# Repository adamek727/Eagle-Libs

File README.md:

# Eagle-Libs
My set of eagle libraries

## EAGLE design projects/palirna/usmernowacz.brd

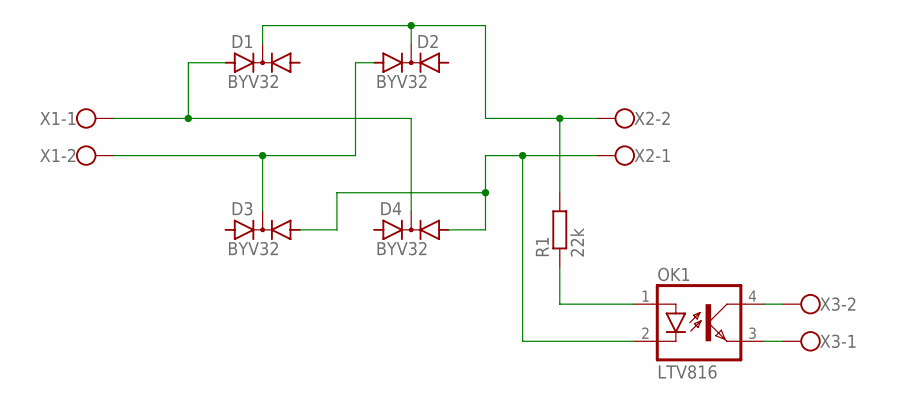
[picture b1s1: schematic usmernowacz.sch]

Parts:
D1, D2, D3, D4: BYV32; TO220ABS
OK1: LTV816; DIL04
R1: 22k; R1206
X1, X2, X3: W237-102

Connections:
unnamed: D1.A1, D4.C, X1.1
unnamed: D1.C, D2.C, R1.2, X2.2
unnamed: D2.A1, D3.C, X1.2
unnamed: D3.A2, D4.A2, OK1.2 (C), X2.1
unnamed: OK1.1 (A), R1.1
unnamed: OK1.3 (EMIT), X3.1
unnamed: OK1.4 (COL), X3.2

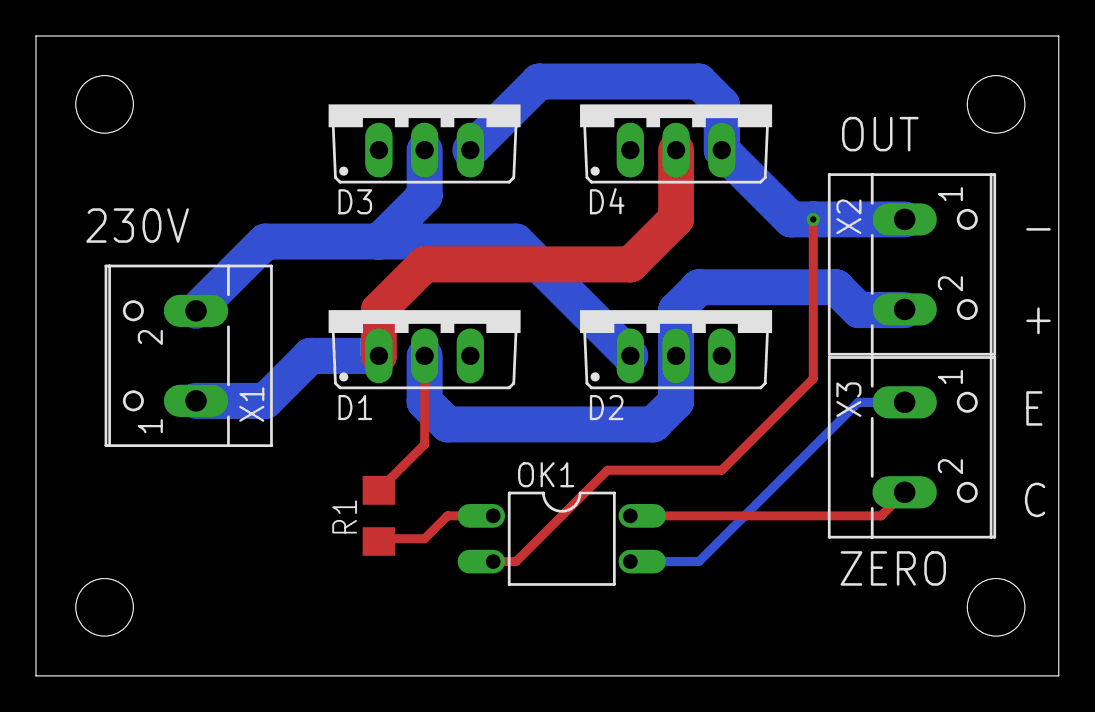
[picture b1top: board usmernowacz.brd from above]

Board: 2 copper layers, 56.8 x 35.5 mm, 9 parts (0 on the bottom side), 7 nets.

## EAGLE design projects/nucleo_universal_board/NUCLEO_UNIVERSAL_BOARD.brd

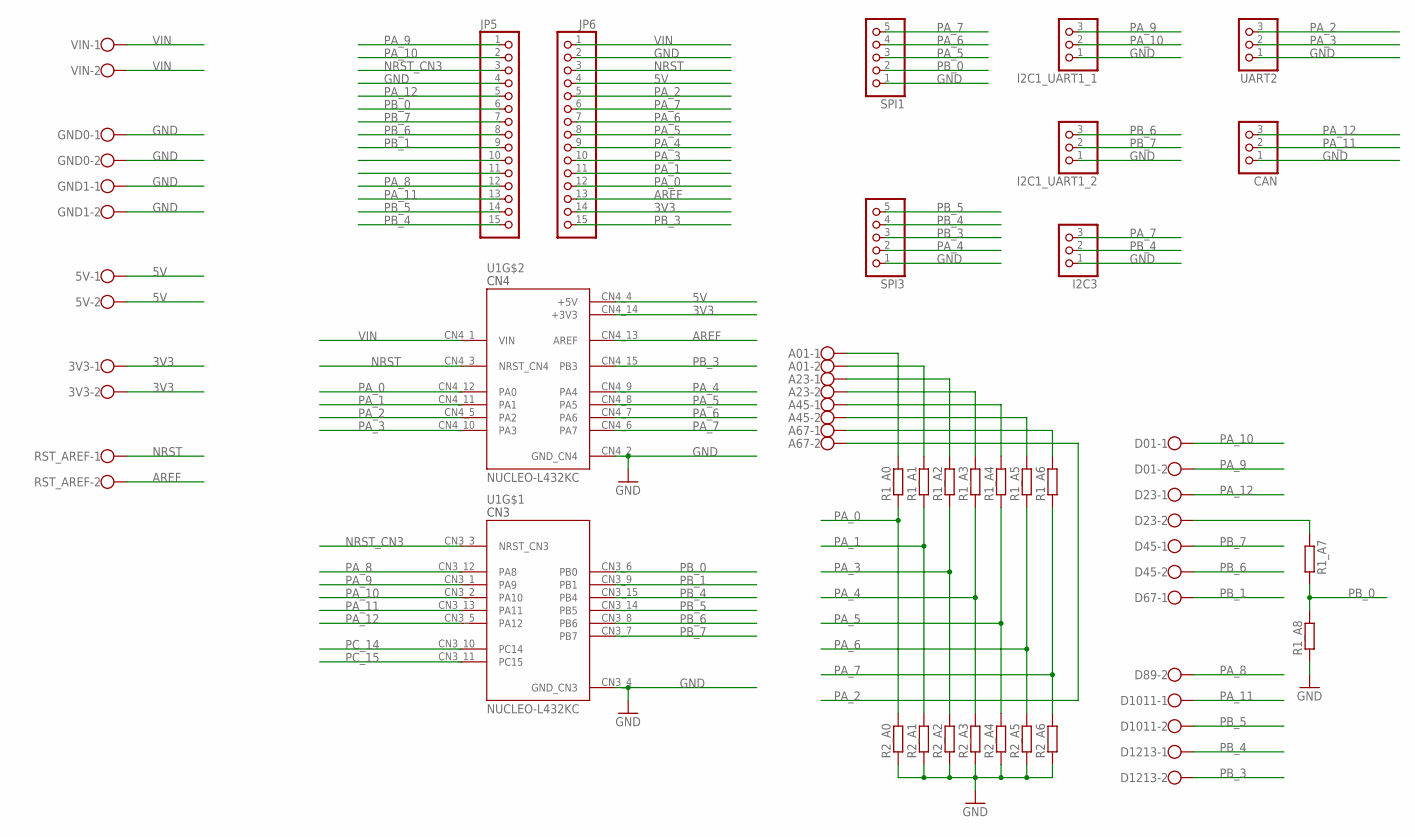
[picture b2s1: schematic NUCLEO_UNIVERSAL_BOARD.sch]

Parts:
3V3, 5V: W237-102
A01, A23, A45, A67: W237-102
CAN: PINHD-1X3; 1X03
D01, D23, D45, D67, D89, D1011, D1213: W237-102
GND0, GND1: W237-102
I2C1_UART1_1, I2C1_UART1_2, I2C3: PINHD-1X3; 1X03
JP5, JP6: PINHD-1X15; 1X15
R1_A0, R1_A1, R1_A2, R1_A3, R1_A4, R1_A5, R1_A6, R1_A7, R1_A8, R2_A0, R2_A1, R2_A2, R2_A3, R2_A4, R2_A5, R2_A6: R-EU_M1206; M1206
RST_AREF: W237-102
SPI1, SPI3: PINHD-1X5; 1X05
U1: NUCLEO-L432KC; MODULE_NUCLEO-L432KC
UART2: PINHD-1X3; 1X03
VIN: W237-102

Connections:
3V3: 3V3.1, 3V3.2, JP6.14, U1.CN4_14 (+3V3)
5V: 5V.1, 5V.2, JP6.4, U1.CN4_4 (+5V)
AREF: JP6.13, RST_AREF.2, U1.CN4_13 (AREF)
GND: CAN.1, GND0.1, GND0.2, GND1.1, GND1.2, I2C1_UART1_1.1, I2C1_UART1_2.1, I2C3.1, JP5.4, JP6.2, R1_A8.1, R2_A0.1, R2_A1.1, R2_A2.1, R2_A3.1, R2_A4.1, R2_A5.1, R2_A6.1, SPI1.1, SPI3.1, U1.CN3_4 (GND_CN3), U1.CN4_2 (GND_CN4), UART2.1
unnamed: D23.2, R1_A7.1
unnamed: A67.1, R1_A6.2
unnamed: A45.2, R1_A5.2
unnamed: A45.1, R1_A4.2
unnamed: A23.2, R1_A3.2
unnamed: A23.1, R1_A2.2
unnamed: A01.2, R1_A1.2
unnamed: A01.1, R1_A0.2
NRST: JP6.3, RST_AREF.1, U1.CN4_3 (NRST_CN4)
NRST_CN3: JP5.3, U1.CN3_3 (NRST_CN3)
PA_0: JP6.12, R1_A0.1, R2_A0.2, U1.CN4_12 (PA0)
PA_1: JP6.11, R1_A1.1, R2_A1.2, U1.CN4_11 (PA1)
PA_2: A67.2, JP6.5, U1.CN4_5 (PA2), UART2.3
PA_3: JP6.10, R1_A2.1, R2_A2.2, U1.CN4_10 (PA3), UART2.2
PA_4: JP6.9, R1_A3.1, R2_A3.2, SPI3.2, U1.CN4_9 (PA4)
PA_5: JP6.8, R1_A4.1, R2_A4.2, SPI1.3, U1.CN4_8 (PA5)
PA_6: JP6.7, R1_A5.1, R2_A5.2, SPI1.4, U1.CN4_7 (PA6)
PA_7: I2C3.3, JP6.6, R1_A6.1, R2_A6.2, SPI1.5, U1.CN4_6 (PA7)
PA_8: D89.2, JP5.12, U1.CN3_12 (PA8)
PA_9: D01.2, I2C1_UART1_1.3, JP5.1, U1.CN3_1 (PA9)
PA_10: D01.1, I2C1_UART1_1.2, JP5.2, U1.CN3_2 (PA10)
PA_11: CAN.2, D1011.1, JP5.13, U1.CN3_13 (PA11)
PA_12: CAN.3, D23.1, JP5.5, U1.CN3_5 (PA12)
PB_0: JP5.6, R1_A7.2, R1_A8.2, SPI1.2, U1.CN3_6 (PB0)
PB_1: D67.1, JP5.9, U1.CN3_9 (PB1)
PB_3: D1213.2, JP6.15, SPI3.3, U1.CN4_15 (PB3)
PB_4: D1213.1, I2C3.2, JP5.15, SPI3.4, U1.CN3_15 (PB4)
PB_5: D1011.2, JP5.14, SPI3.5, U1.CN3_14 (PB5)
PB_6: D45.2, I2C1_UART1_2.3, JP5.8, U1.CN3_8 (PB6)
PB_7: D45.1, I2C1_UART1_2.2, JP5.7, U1.CN3_7 (PB7)
PC_14: U1.CN3_10 (PC14)
PC_15: U1.CN3_11 (PC15)
VIN: JP6.1, U1.CN4_1 (VIN), VIN.1, VIN.2

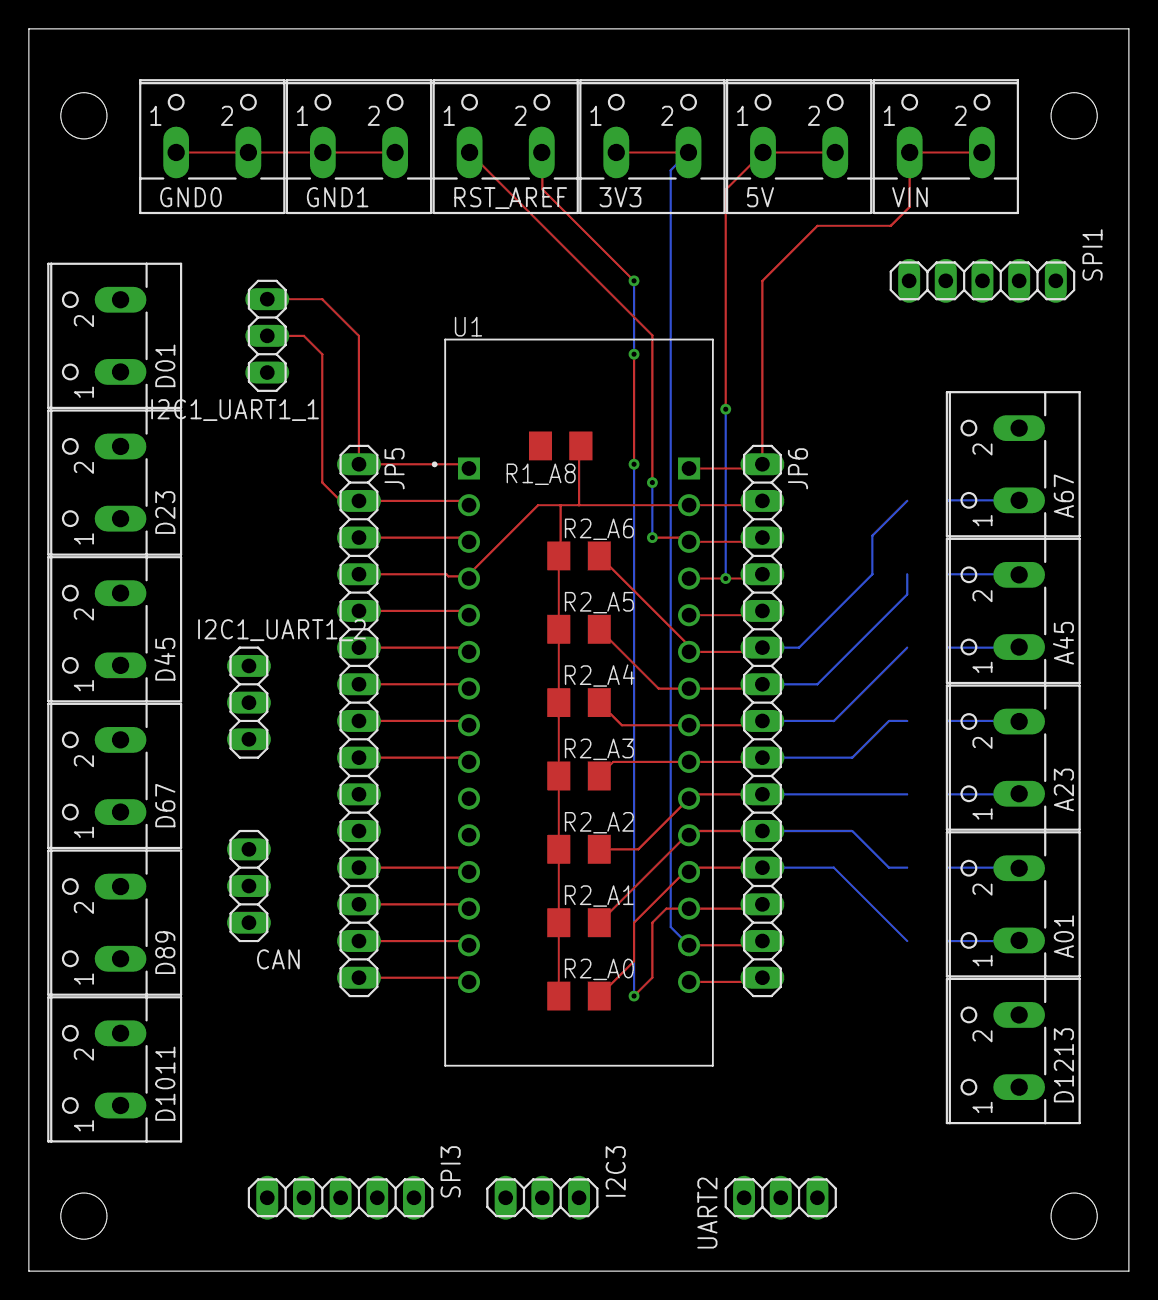
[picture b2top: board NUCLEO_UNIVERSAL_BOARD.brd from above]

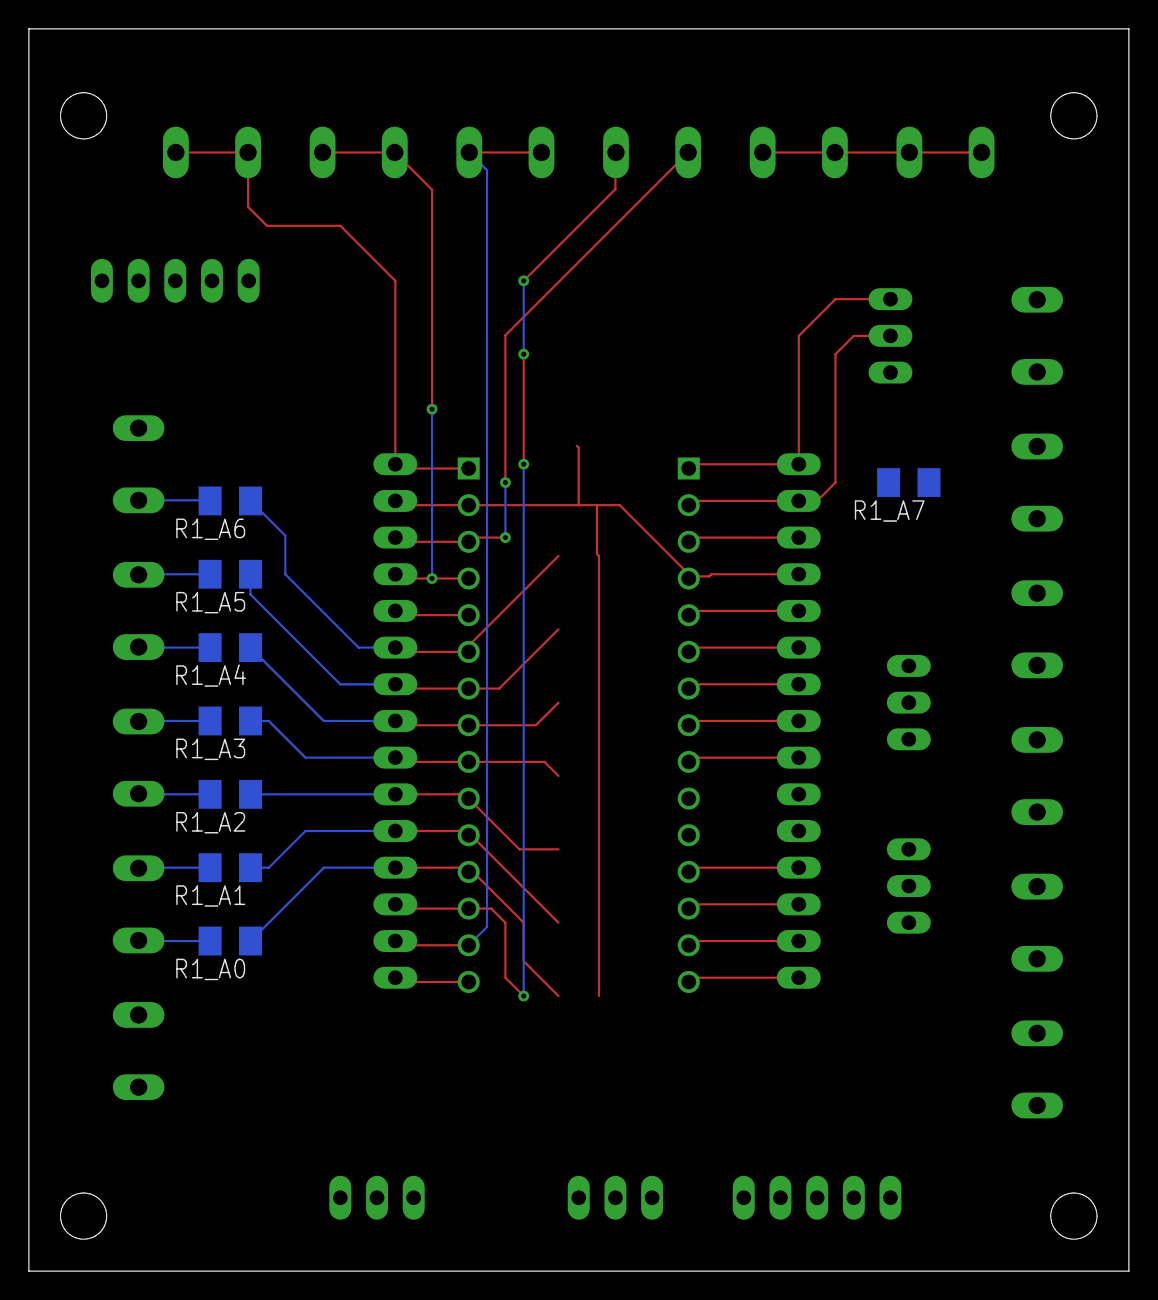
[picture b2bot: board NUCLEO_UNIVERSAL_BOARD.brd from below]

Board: 2 copper layers, 76.2 x 86.0 mm, 43 parts (8 on the bottom side), 35 nets.

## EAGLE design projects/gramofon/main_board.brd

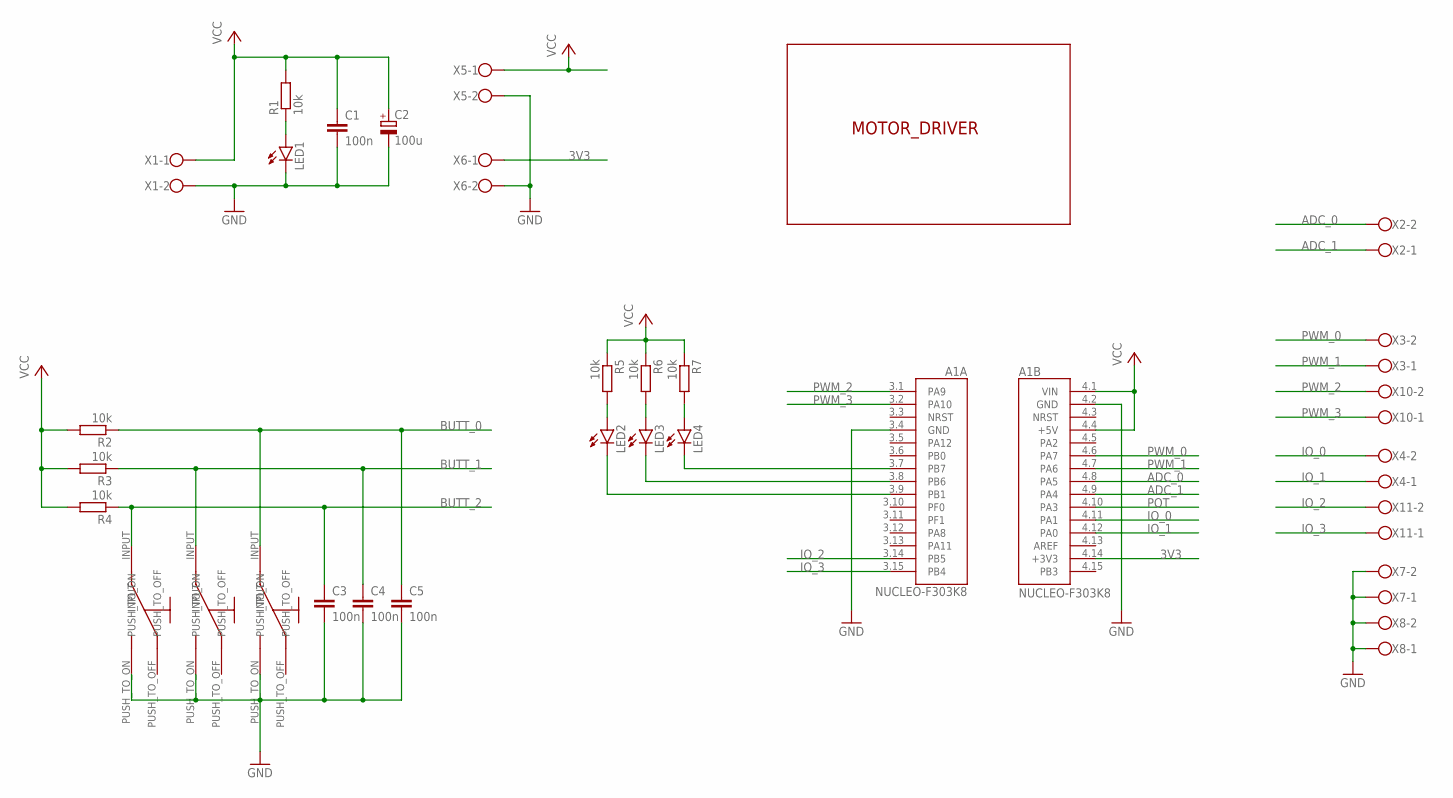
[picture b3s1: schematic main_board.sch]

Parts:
A1: NUCLEO-F303K8; MODULE_NUCLEO-F303K8
C1, C3, C4, C5: 100n; C1206
C2: 100u; 150CLZ-1010
LED1: LEDSMT1206; 1206
LED2, LED3, LED4: LEDCHIPLED_1206; CHIPLED_1206
R1, R2, R3, R4, R5, R6, R7: 10k; R1206
U$2, U$3, U$4: BUTTON
U$5: MOTOR_DRIVER
X1, X2, X3, X4, X5, X6, X7, X8, X10, X11: W237-102

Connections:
3V3: A1.4.14 (+3V3), X6.1
ADC_0: A1.4.8 (PA5), X2.2
ADC_1: A1.4.9 (PA4), X2.1
BUTT_0: C5.1, R2.1, U$4.INPUT
BUTT_1: C4.1, R3.1, U$2.INPUT
BUTT_2: C3.1, R4.1, U$3.INPUT
GND: A1.3.4 (GND), A1.4.2 (GND), C1.2, C2.-, C3.2, C4.2, C5.2, LED1.C, U$2.PUSH_TO_ON, U$3.PUSH_TO_ON, U$4.PUSH_TO_ON, X1.2, X5.2, X6.2, X7.1, X7.2, X8.1, X8.2
IO_0: A1.4.11 (PA1), X4.2
IO_1: A1.4.12 (PA0), X4.1
IO_2: A1.3.14 (PB5), X11.2
IO_3: A1.3.15 (PB4), X11.1
unnamed: A1.3.9 (PB1), LED2.C
unnamed: A1.3.8 (PB6), LED3.C
unnamed: A1.3.7 (PB7), LED4.C
unnamed: LED1.A, R1.1
unnamed: LED4.A, R7.2
unnamed: LED3.A, R6.2
unnamed: LED2.A, R5.2
POT: A1.4.10 (PA3)
PWM_0: A1.4.6 (PA7), X3.2
PWM_1: A1.4.7 (PA6), X3.1
PWM_2: A1.3.1 (PA9), X10.2
PWM_3: A1.3.2 (PA10), X10.1
VCC: A1.4.1 (VIN), A1.4.4 (+5V), C1.1, C2.+, R1.2, R2.2, R3.2, R4.2, R5.1, R6.1, R7.1, X1.1, X5.1

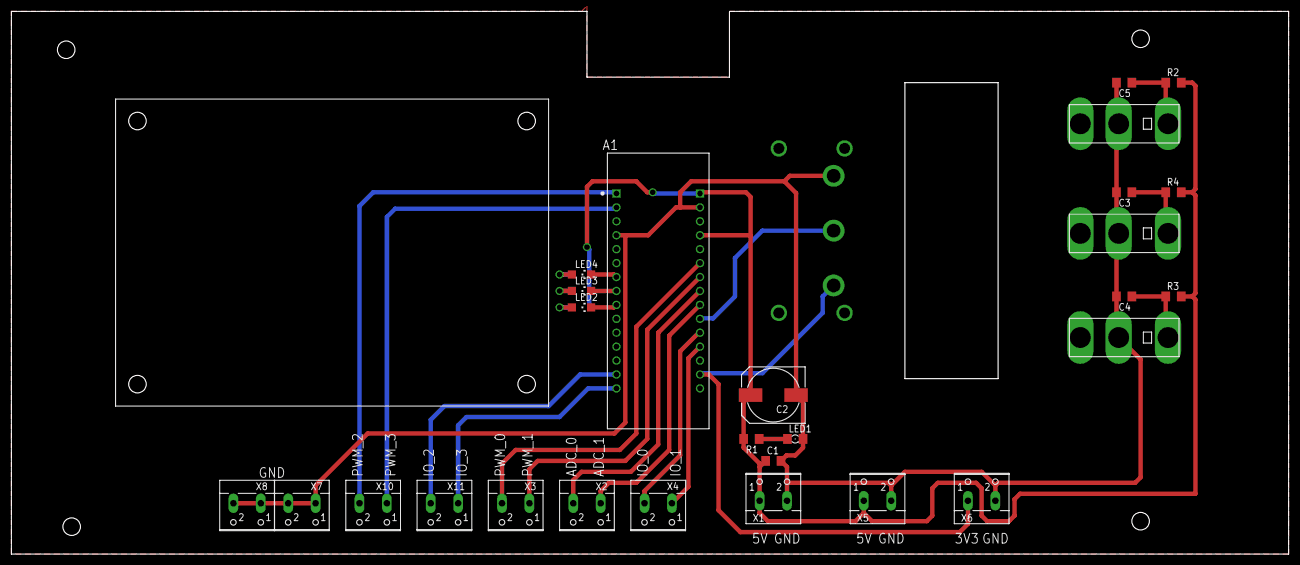
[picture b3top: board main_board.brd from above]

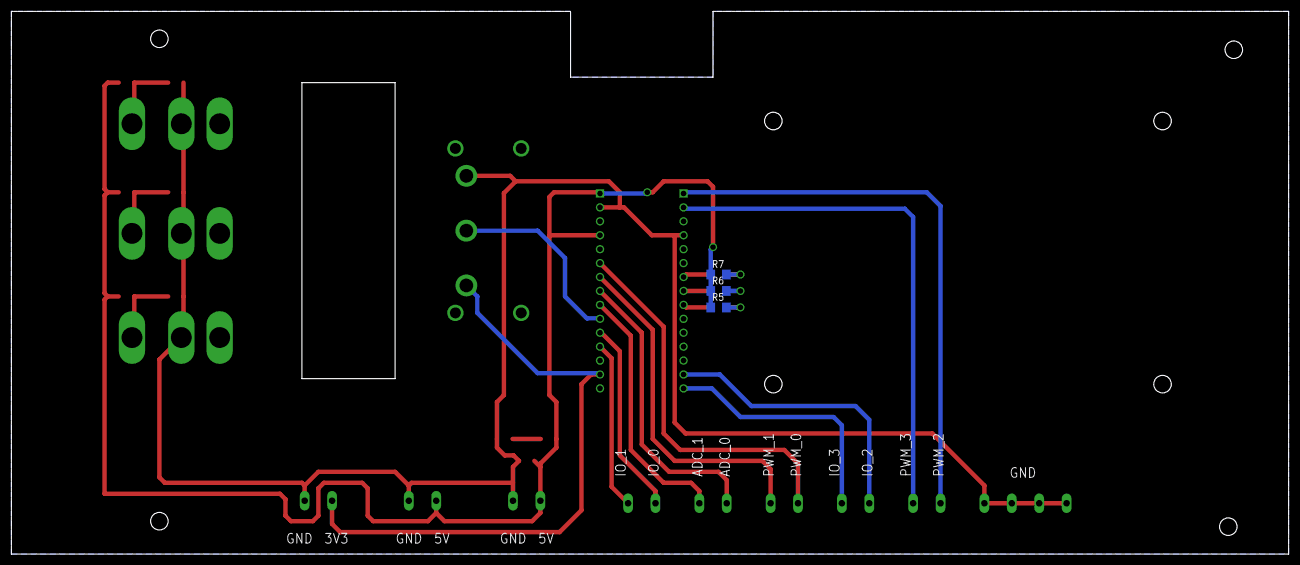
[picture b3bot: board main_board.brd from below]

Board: 2 copper layers, 233.0 x 99.0 mm, 31 parts (3 on the bottom side), 23 nets.

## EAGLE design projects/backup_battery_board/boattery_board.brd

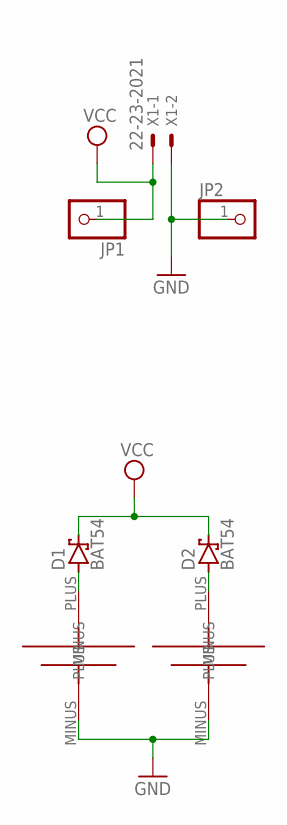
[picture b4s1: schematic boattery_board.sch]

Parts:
D1, D2: BAT54; SOT23
JP1, JP2: PINHD-1X1; 1X01
U$1, U$2: KEYSTONE_1018; KEYSTONE_1018_HOLDER
X1: 22-23-2021

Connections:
GND: JP2.1, U$1.MINUS, U$2.MINUS, X1.2
unnamed: D1.1 (A), U$1.PLUS
unnamed: D2.1 (A), U$2.PLUS
VCC: D1.3 (C), D2.3 (C), JP1.1, X1.1

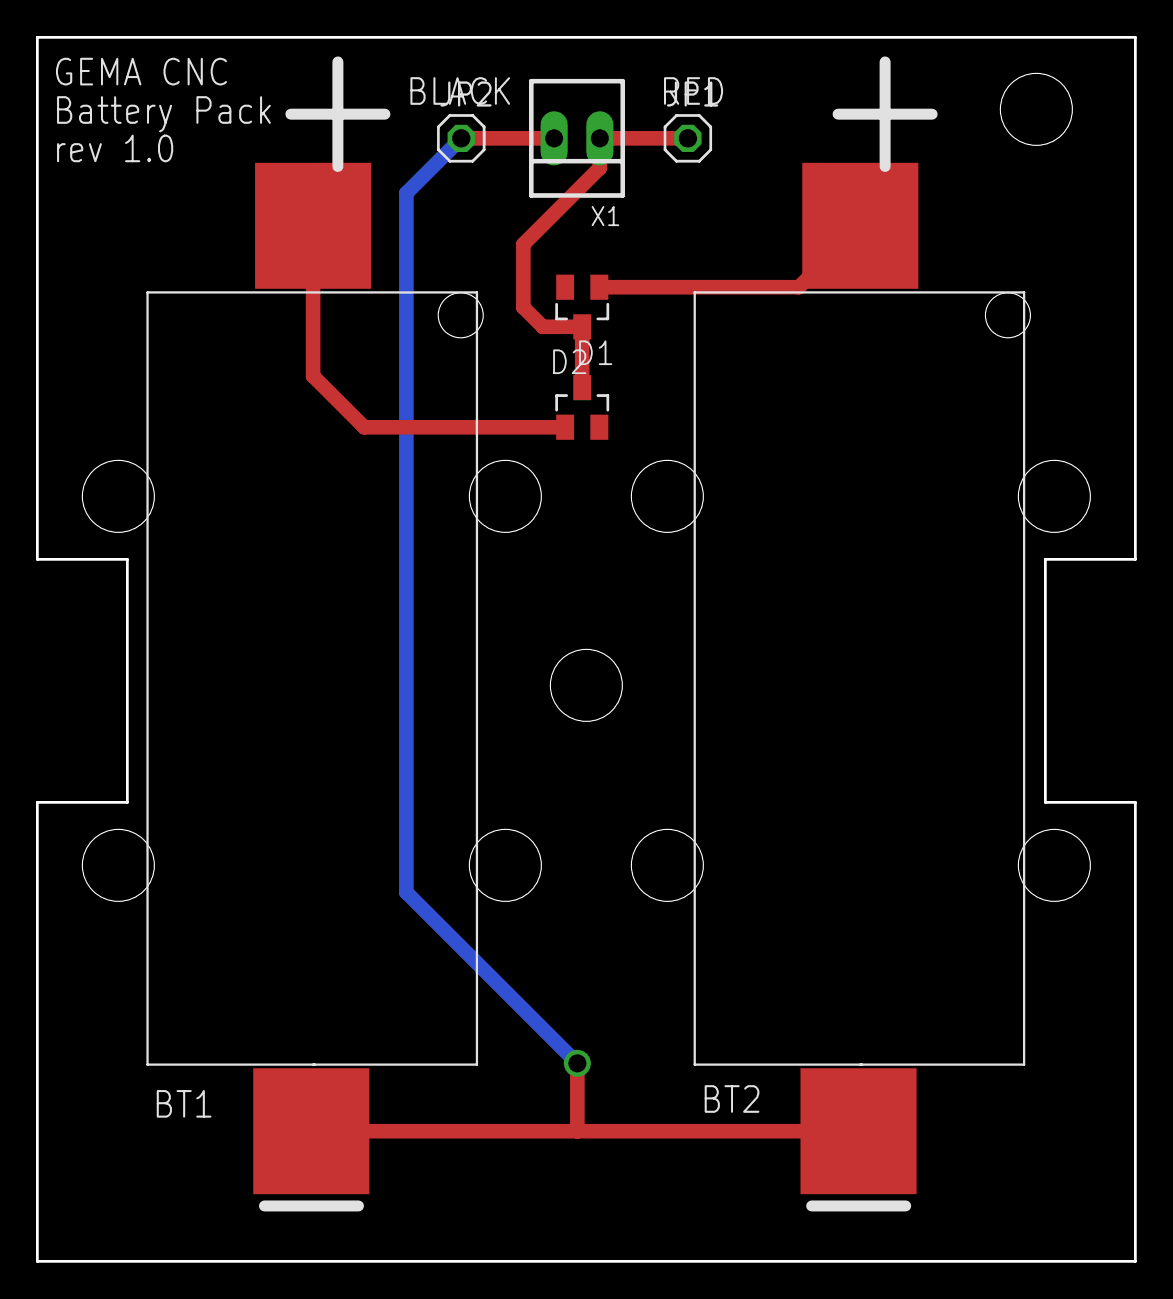
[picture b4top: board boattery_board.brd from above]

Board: 2 copper layers, 61.0 x 68.0 mm, 7 parts (0 on the bottom side), 4 nets.

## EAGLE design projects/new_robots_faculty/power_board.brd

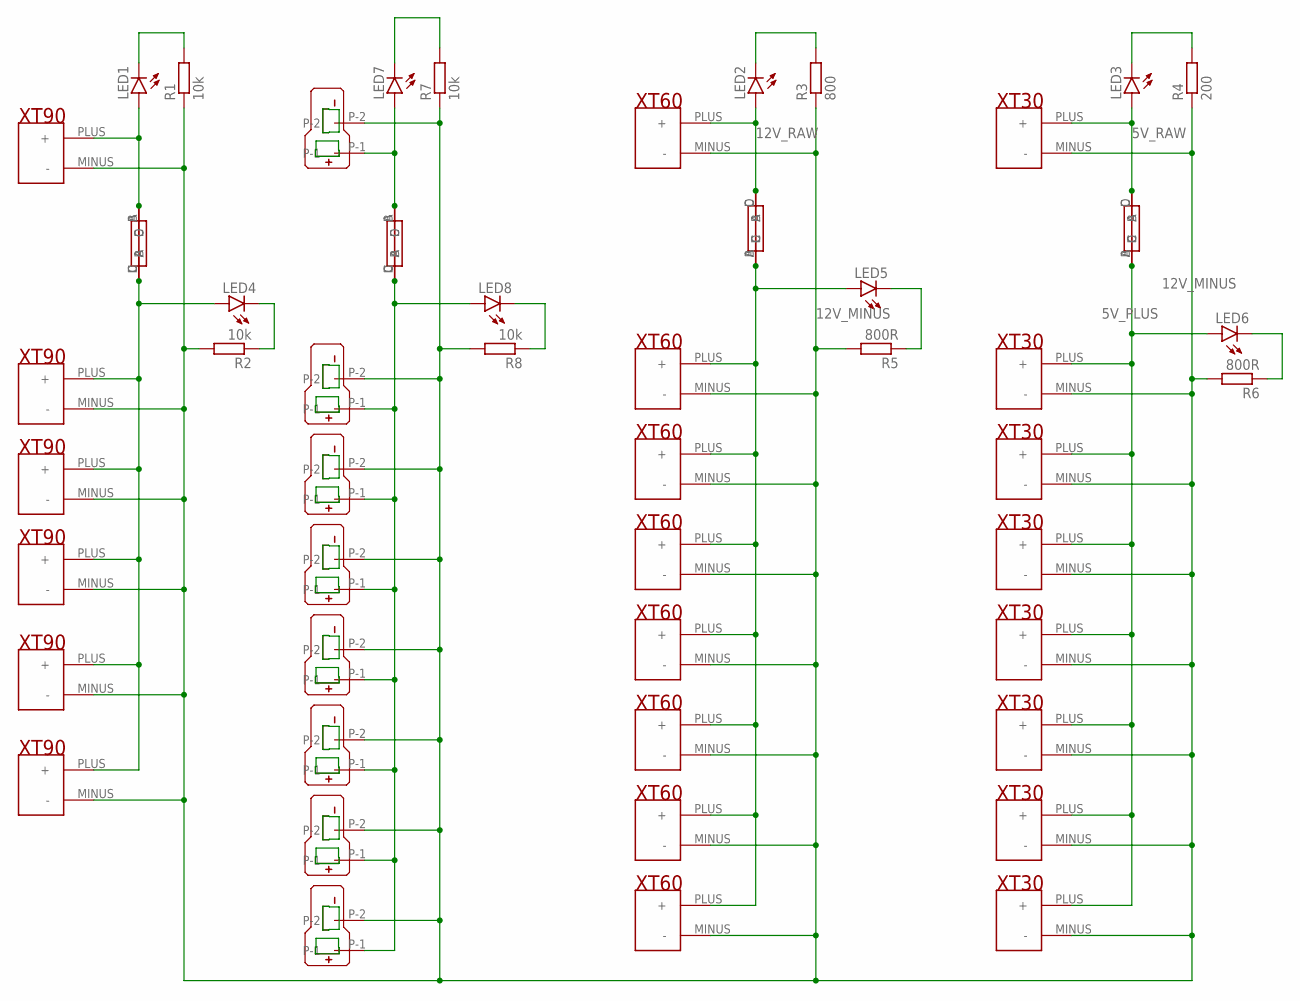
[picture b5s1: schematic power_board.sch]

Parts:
LED1, LED2, LED3, LED4, LED5, LED6, LED7, LED8: LED5MM
R1, R2, R7, R8: 10k; M1206
R3: 800; M1206
R4: 200; M1206
R5, R6: 800R; M1206
U$1, U$2, U$3, U$4, U$24, U$34: XT90; XT90_FOOTPRINT
U$5, U$6, U$7, U$8, U$9, U$10, U$11, U$12: XT60; XT60_FOOTPRINT
U$13, U$14, U$15, U$16, U$17, U$18, U$19, U$20: XT30; XT30_FOOTPRINT
U$21, U$22, U$23, U$30: AUTOFUSE; AUTOFUSE_HOLDER
U$25, U$26, U$27, U$28, U$29, U$31, U$32, U$33: T-PLUG_CONNECTOR; T_PLUG_CONNECTOR

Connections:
5V_PLUS: LED6.A, U$14.PLUS (+), U$15.PLUS (+), U$16.PLUS (+), U$17.PLUS (+), U$18.PLUS (+), U$19.PLUS (+), U$20.PLUS (+), U$23.A, U$23.B
5V_RAW: LED3.A, U$13.PLUS (+), U$23.C, U$23.D
12V_MINUS: R1.1, R2.2, R3.1, R4.1, R5.2, R6.2, R7.1, R8.2, U$1.MINUS (-), U$2.MINUS (-), U$3.MINUS (-), U$4.MINUS (-), U$5.MINUS (-), U$6.MINUS (-), U$7.MINUS (-), U$8.MINUS (-), U$9.MINUS (-), U$10.MINUS (-), U$11.MINUS (-), U$12.MINUS (-), U$13.MINUS (-), U$14.MINUS (-), U$15.MINUS (-), U$16.MINUS (-), U$17.MINUS (-), U$18.MINUS (-), U$19.MINUS (-), U$20.MINUS (-), U$24.MINUS (-), U$25.P-2, U$26.P-2, U$27.P-2, U$28.P-2, U$29.P-2, U$31.P-2, U$32.P-2, U$33.P-2, U$34.MINUS (-)
12V_PLUS: LED5.A, U$6.PLUS (+), U$7.PLUS (+), U$8.PLUS (+), U$9.PLUS (+), U$10.PLUS (+), U$11.PLUS (+), U$12.PLUS (+), U$22.A, U$22.B
12V_RAW: LED2.A, U$5.PLUS (+), U$22.C, U$22.D
BATT_PLUS: LED4.A, U$2.PLUS (+), U$3.PLUS (+), U$4.PLUS (+), U$21.C, U$21.D, U$24.PLUS (+), U$34.PLUS (+)
BATT_RAW: LED1.A, U$1.PLUS (+), U$21.A, U$21.B
unnamed: LED1.K (C), R1.2
unnamed: LED5.K (C), R5.1
unnamed: LED3.K (C), R4.2
unnamed: LED6.K (C), R6.1
unnamed: LED4.K (C), R2.1
unnamed: LED2.K (C), R3.2
unnamed: LED7.A, U$25.P-1, U$30.A, U$30.B
unnamed: LED7.K (C), R7.2
unnamed: LED8.A, U$26.P-1, U$27.P-1, U$28.P-1, U$29.P-1, U$30.C, U$30.D, U$31.P-1, U$32.P-1, U$33.P-1
unnamed: LED8.K (C), R8.1

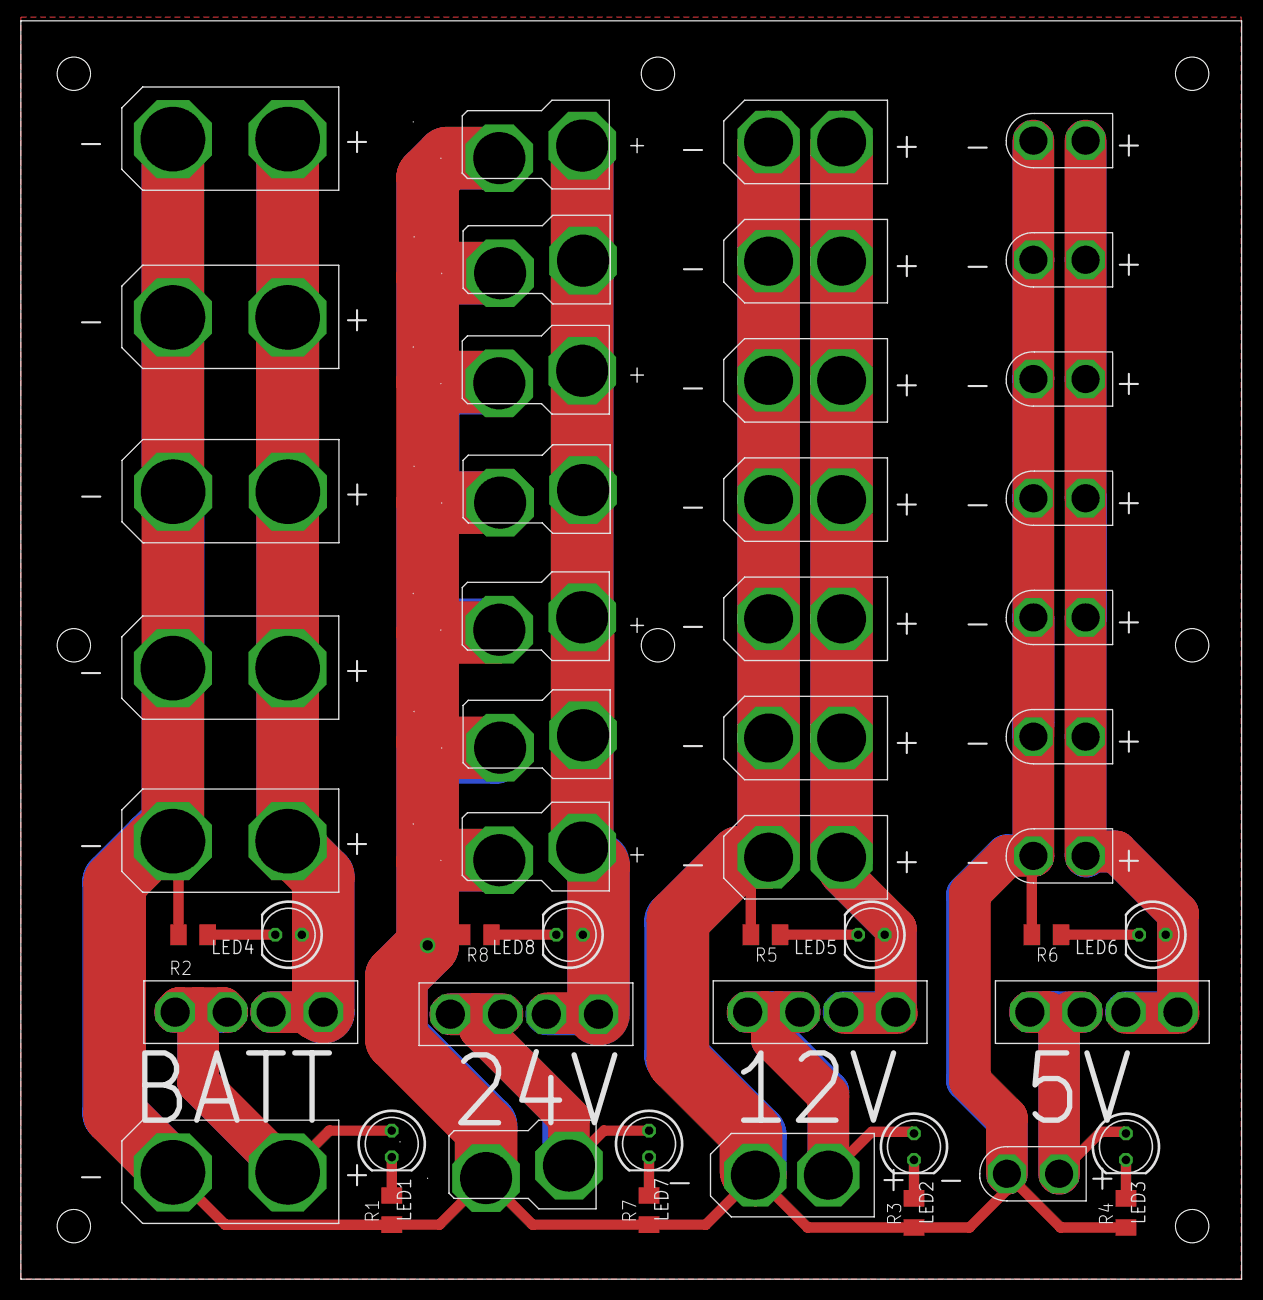
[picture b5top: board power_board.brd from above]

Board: 2 copper layers, 117.0 x 120.6 mm, 50 parts (0 on the bottom side), 17 nets.

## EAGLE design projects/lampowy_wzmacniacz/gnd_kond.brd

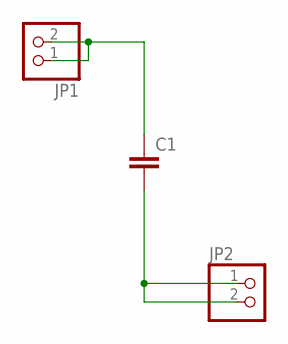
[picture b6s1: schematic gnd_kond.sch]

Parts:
C1: C-EU150-091X182; C150-091X182
JP1, JP2: PINHD-1X2; 1X02

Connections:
unnamed: C1.1, JP1.1, JP1.2
unnamed: C1.2, JP2.1, JP2.2

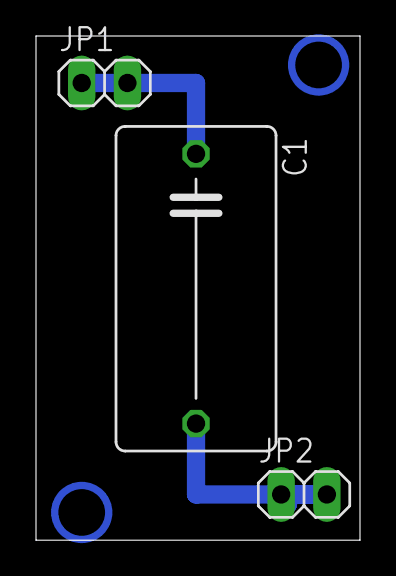
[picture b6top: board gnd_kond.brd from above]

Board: 2 copper layers, 18.0 x 28.0 mm, 3 parts (0 on the bottom side), 2 nets.

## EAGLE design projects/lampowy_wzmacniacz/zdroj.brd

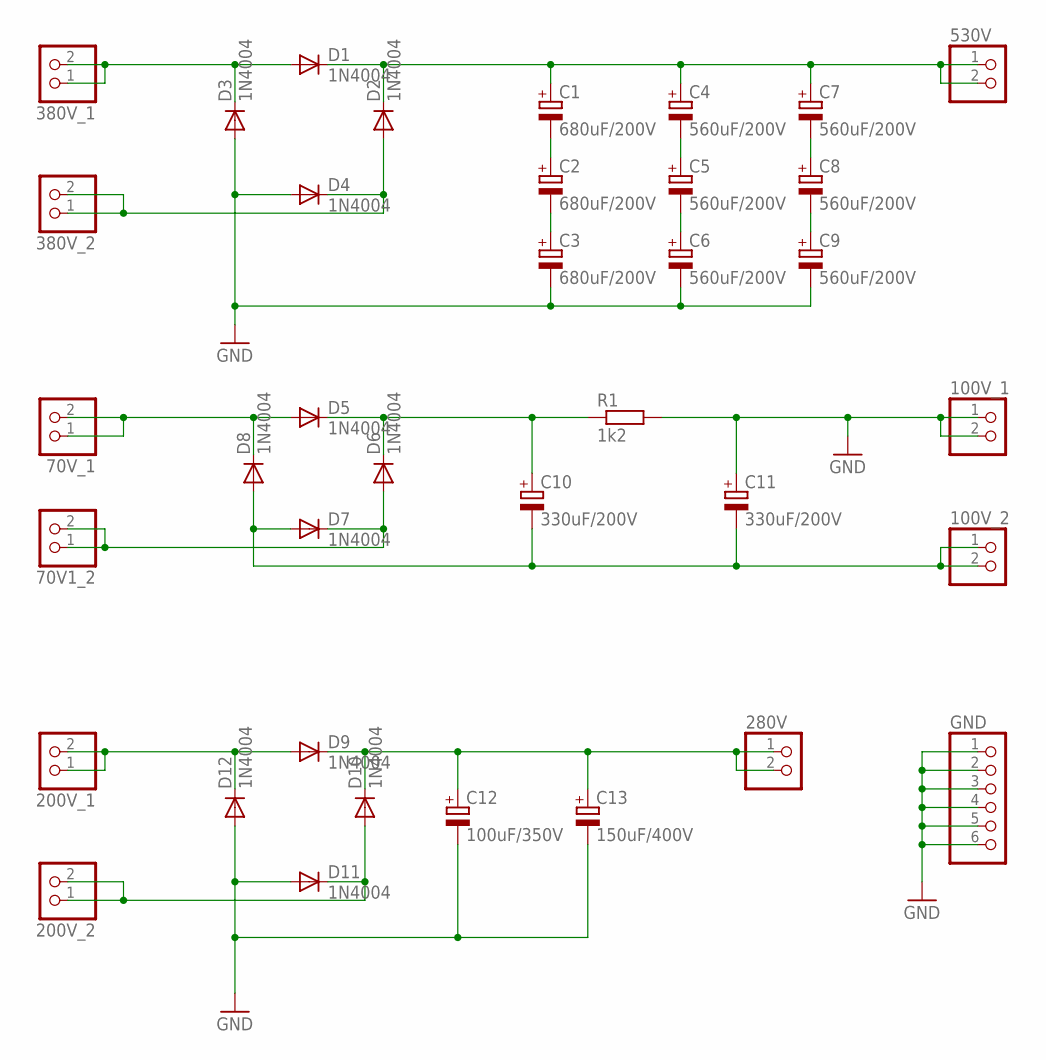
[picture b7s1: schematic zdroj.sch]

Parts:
70V1_2, 70V_1, 100V_1, 100V_2, 200V_1, 200V_2, 280V, 380V_1, 380V_2, 530V: 1X02
C1, C2, C3: 680uF/200V; EB22,5D
C4, C5, C6, C7, C8, C9: 560uF/200V; EB22,5D
C10, C11: 330uF/200V; EB22,5D
C12: 100uF/350V; E7,5-18
C13: 150uF/400V; E7,5-18
D1, D2, D3, D4, D5, D6, D7, D8, D9, D10, D11, D12: 1N4004; DO41-10
GND: 1X06
R1: 1k2; 0309/12

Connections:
GND: 100V_1.1, 100V_1.2, C3.-, C6.-, C9.-, C11.+, C12.-, C13.-, D3.A, D4.A, D11.A, D12.A, GND.1, GND.2, GND.3, GND.4, GND.5, GND.6, R1.2
unnamed: 380V_1.1, 380V_1.2, D1.A, D3.C
unnamed: 530V.1, 530V.2, C1.+, C4.+, C7.+, D1.C, D2.C
unnamed: 380V_2.1, 380V_2.2, D2.A, D4.C
unnamed: C7.-, C8.+
unnamed: 70V_1.1, 70V_1.2, D5.A, D8.C
unnamed: C10.+, D5.C, D6.C, R1.1
unnamed: 70V1_2.1, 70V1_2.2, D6.A, D7.C
unnamed: C8.-, C9.+
unnamed: 200V_1.1, 200V_1.2, D9.A, D12.C
unnamed: 280V.1, 280V.2, C12.+, C13.+, D9.C, D10.C
unnamed: 200V_2.1, 200V_2.2, D10.A, D11.C
unnamed: C1.-, C2.+
unnamed: C4.-, C5.+
unnamed: C2.-, C3.+
unnamed: C5.-, C6.+
unnamed: 100V_2.1, 100V_2.2, C10.-, C11.-, D7.A, D8.A

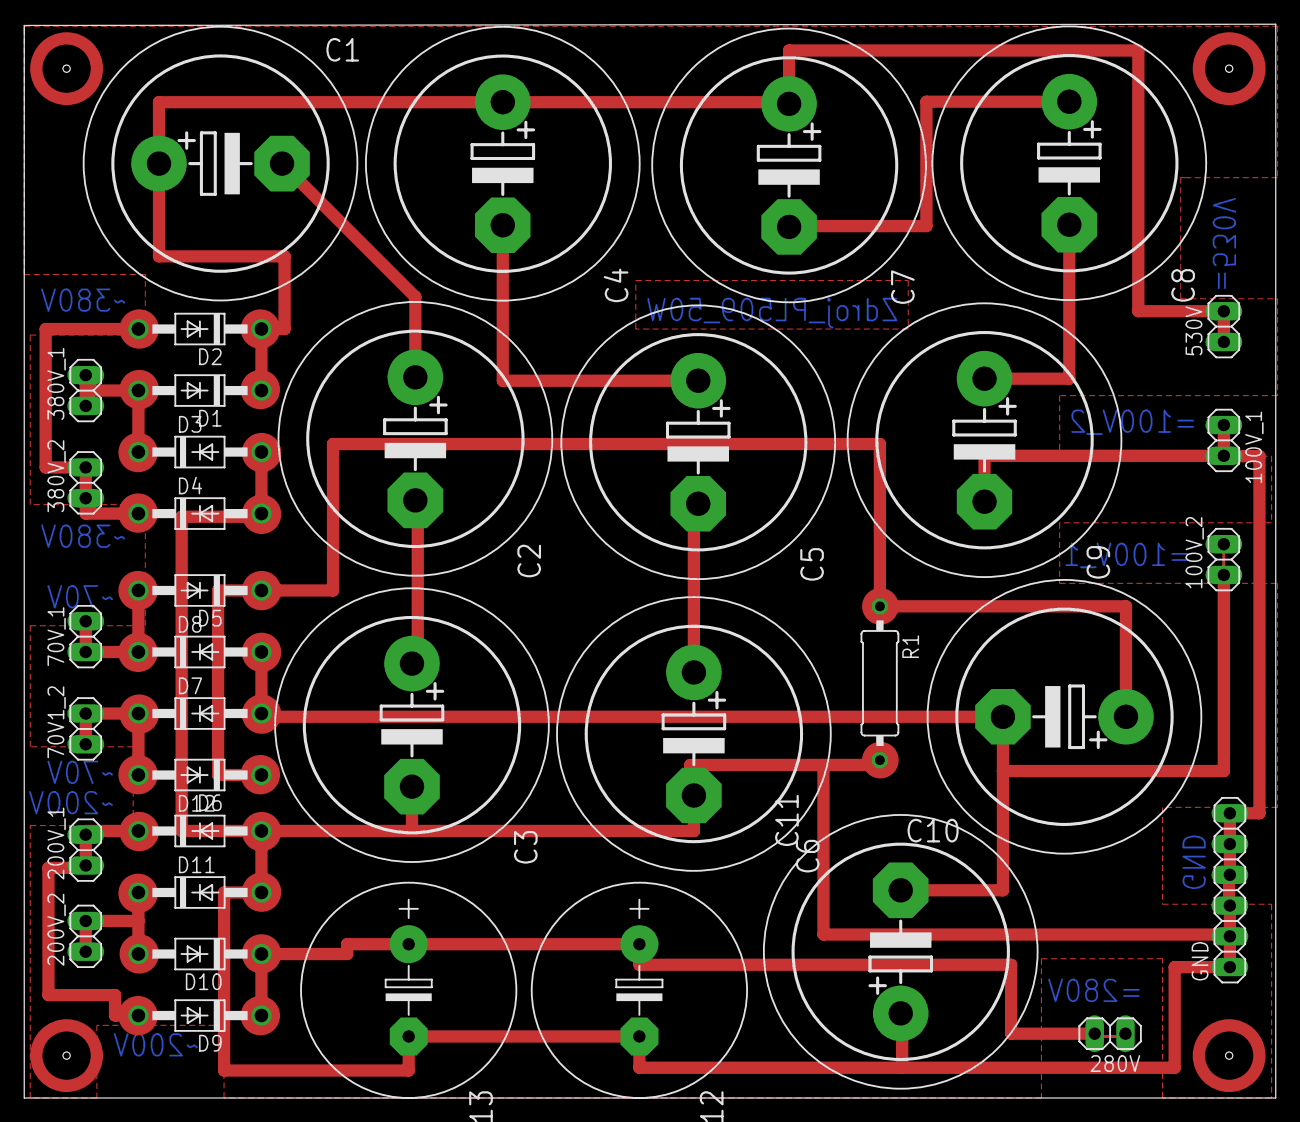
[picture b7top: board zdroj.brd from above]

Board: 2 copper layers, 103.3 x 88.7 mm, 37 parts (0 on the bottom side), 17 nets.
